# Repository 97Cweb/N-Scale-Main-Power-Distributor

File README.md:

Main Power Distributor 

I supply these as is. You still need to use sense using them. If you burn down your place or hurt yourself, that's on you

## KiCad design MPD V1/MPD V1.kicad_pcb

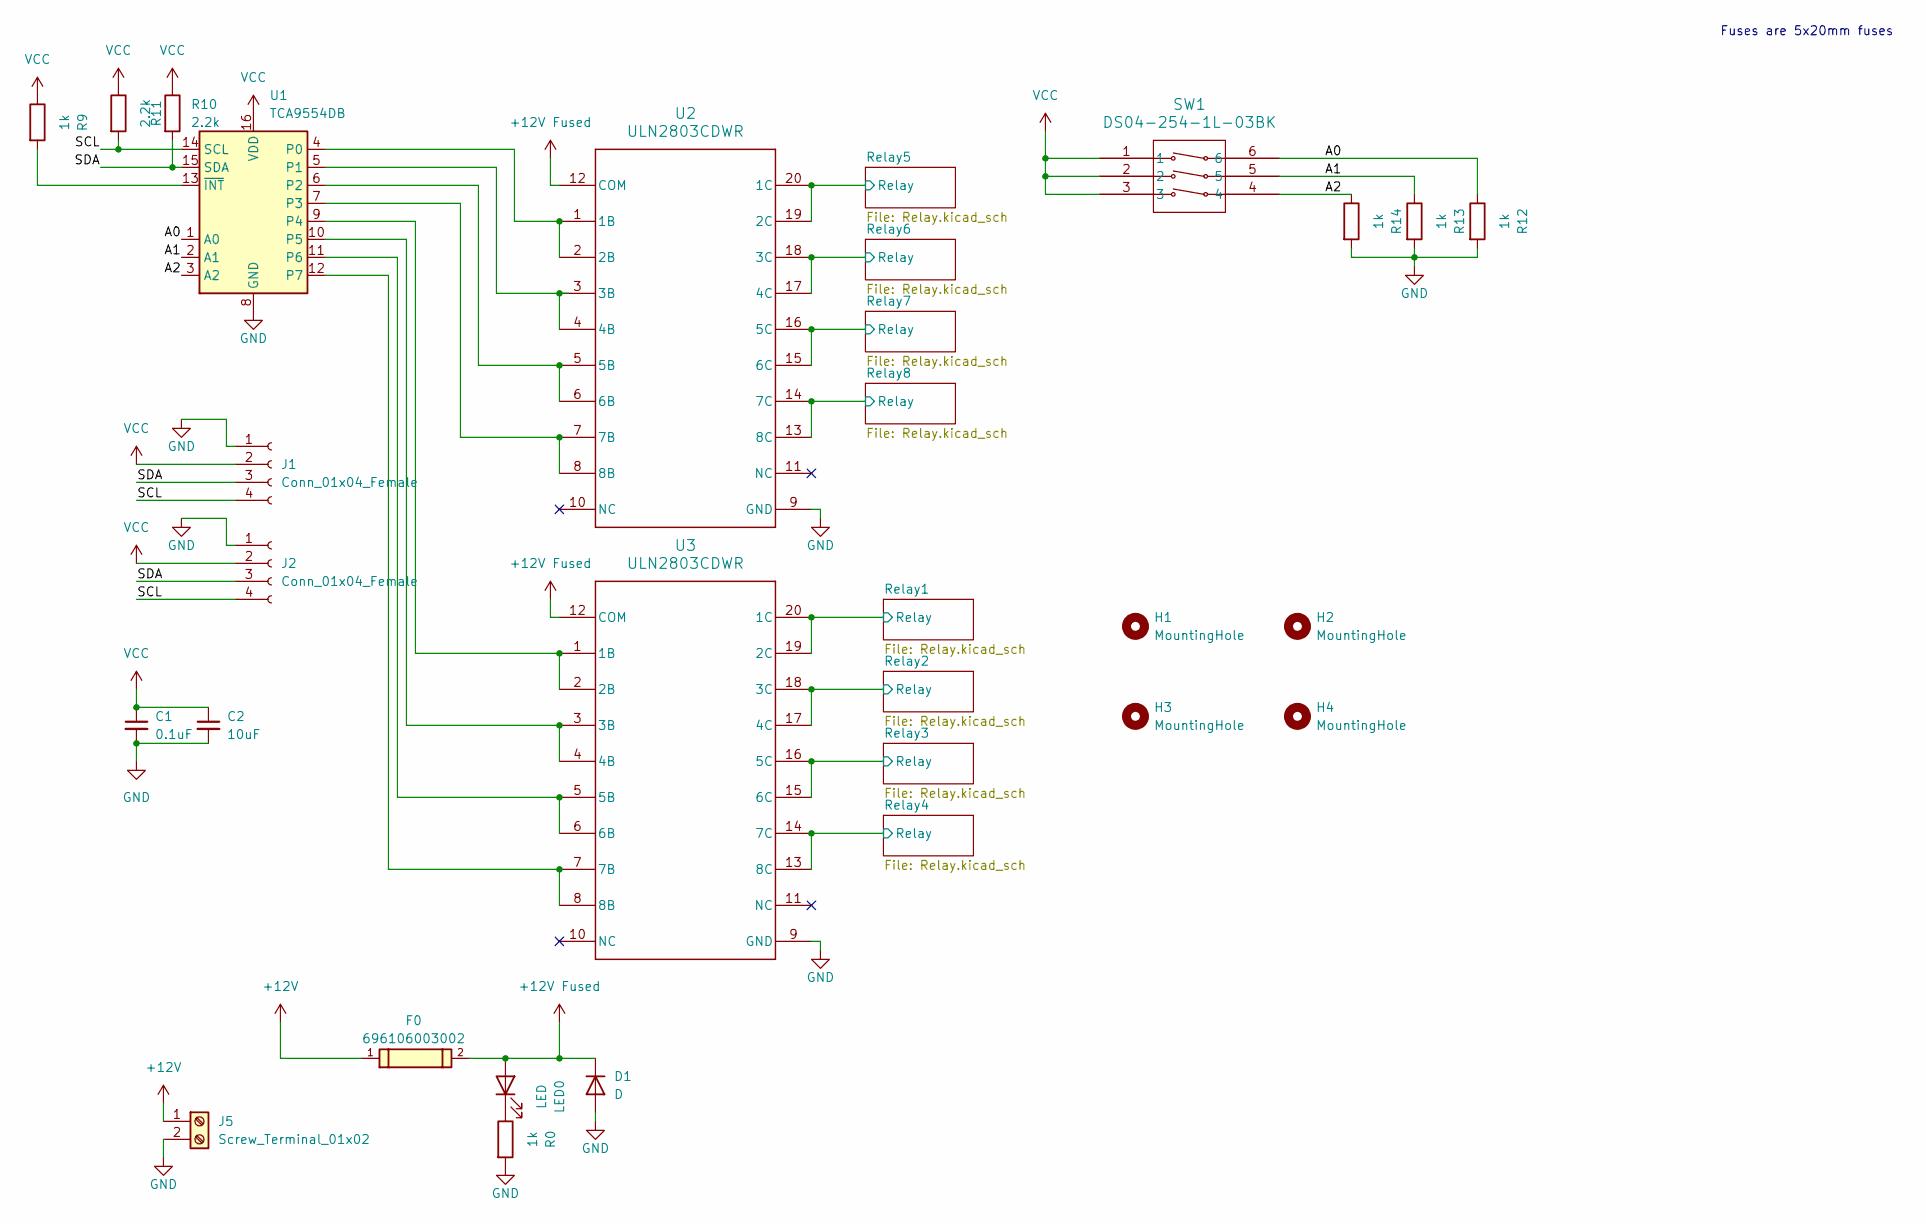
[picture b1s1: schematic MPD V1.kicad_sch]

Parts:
C1: 0.1uF; C_0603_1608Metric_Pad1.08x0.95mm_HandSolder
C2: 10uF; C_0603_1608Metric_Pad1.08x0.95mm_HandSolder
D1: D; D_A-405_P12.70mm_Horizontal
F0: 696106003002; PART-NUMBER 696106003002
H1, H2, H3, H4: MountingHole; MountingHole_3.2mm_M3
J1, J2: Conn_01x04_Female; JST_SH_SM04B-SRSS-TB_1x04-1MP_P1.00mm_Horizontal
J5: Screw_Terminal_01x02; TerminalBlock_bornier-2_P5.08mm
LED0: LED; LED_D5.0mm
R0, R9, R12, R13, R14: 1k; R_1206_3216Metric_Pad1.30x1.75mm_HandSolder
R10, R11: 2.2k; R_1206_3216Metric_Pad1.30x1.75mm_HandSolder
SW1: DS04-254-1L-03BK; DS04-254_CUD
U1: TCA9554DB; SSOP-16_5.3x6.2mm_P0.65mm
U2, U3: ULN2803CDWR; DW0020A-IPC_A

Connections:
+12V: F0.1, J5.1
+12V Fused: D1.1 (K), F0.2, LED0.2 (A), U2.12 (COM), U3.12 (COM); also elsewhere on the board
/A0: R12.1, SW1.6, U1.1 (A0)
/A1: R13.1, SW1.5, U1.2 (A1)
/A2: R14.1, SW1.4, U1.3 (A2)
/Relay1/Relay: U3.19 (2C), U3.20 (1C); also elsewhere on the board
/Relay2/Relay: U3.17 (4C), U3.18 (3C); also elsewhere on the board
/Relay3/Relay: U3.15 (6C), U3.16 (5C); also elsewhere on the board
/Relay4/Relay: U3.13 (8C), U3.14 (7C); also elsewhere on the board
/Relay5/Relay: U2.19 (2C), U2.20 (1C); also elsewhere on the board
/Relay6/Relay: U2.17 (4C), U2.18 (3C); also elsewhere on the board
/Relay7/Relay: U2.15 (6C), U2.16 (5C); also elsewhere on the board
/Relay8/Relay: U2.13 (8C), U2.14 (7C); also elsewhere on the board
/SCL: J1.4, J2.4, R11.2, U1.14 (SCL)
/SDA: J1.3, J2.3, R10.2, U1.15 (SDA)
GND: C1.2, C2.2, D1.2 (A), J1.1, J2.1, J5.2, R0.2, R12.2, R13.2, R14.2, U1.8 (GND), U2.9 (GND), U3.9 (GND); also elsewhere on the board
unnamed: LED0.1 (K), R0.1
unnamed: U1.4 (P0), U2.1 (1B), U2.2 (2B)
unnamed: U1.5 (P1), U2.3 (3B), U2.4 (4B)
unnamed: U1.6 (P2), U2.5 (5B), U2.6 (6B)
unnamed: U1.7 (P3), U2.7 (7B), U2.8 (8B)
unnamed: U1.9 (P4), U3.1 (1B), U3.2 (2B)
unnamed: U1.10 (P5), U3.3 (3B), U3.4 (4B)
unnamed: U1.11 (P6), U3.5 (5B), U3.6 (6B)
unnamed: U1.12 (P7), U3.7 (7B), U3.8 (8B)
unnamed: R9.2, U1.13 (~INT)
VCC: C1.1, C2.1, J1.2, J2.2, R9.1, R10.1, R11.1, SW1.1, SW1.2, SW1.3, U1.16 (VDD)

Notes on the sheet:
Fuses are 5x20mm fuses

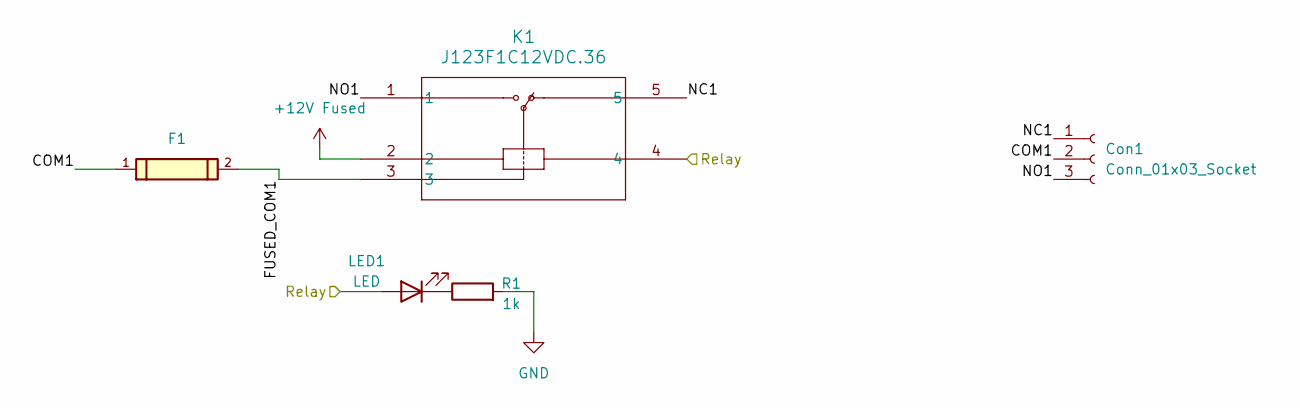
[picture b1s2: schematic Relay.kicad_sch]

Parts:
Con1: Conn_01x03_Socket; CONN_1757255_PXC
F1: 696106003002; PART-NUMBER 696106003002
K1: J123F1C12VDC.36; RELAY5_J123F1C5VDC.36_CRS with Cutout
LED1: LED; LED_D5.0mm
R1: 1k; R_1206_3216Metric_Pad1.30x1.75mm_HandSolder

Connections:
+12V Fused: K1.2; also elsewhere on the board
/Relay1/COM1: Con1.2, F1.1
/Relay1/FUSED_COM1: F1.2, K1.3
/Relay1/NC1: Con1.1, K1.5
/Relay1/NO1: Con1.3, K1.1
/Relay1/Relay: K1.4, LED1.2 (A); also elsewhere on the board
GND: R1.2; also elsewhere on the board
unnamed: LED1.1 (K), R1.1

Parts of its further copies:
Con2, Con3, Con4, Con5, Con6, Con7, Con8: Conn_01x03_Socket; CONN_1757255_PXC
F2, F3, F4, F5, F6, F7, F8: 696106003002; PART-NUMBER 696106003002
K2, K3, K4, K5, K6, K7, K8: J123F1C12VDC.36; RELAY5_J123F1C5VDC.36_CRS with Cutout
LED2, LED3, LED4, LED5, LED6, LED7, LED8: LED; LED_D5.0mm
R2, R3, R4, R5, R6, R7, R8: 1k; R_1206_3216Metric_Pad1.30x1.75mm_HandSolder

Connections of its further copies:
+12V Fused: K2.2, K3.2, K4.2, K5.2, K6.2, K7.2, K8.2; also elsewhere on the board
/Relay2/COM1: Con2.2, F2.1
/Relay2/FUSED_COM1: F2.2, K2.3
/Relay2/NC1: Con2.1, K2.5
/Relay2/NO1: Con2.3, K2.1
/Relay2/Relay: K2.4, LED2.2 (A); also elsewhere on the board
/Relay3/COM1: Con3.2, F3.1
/Relay3/FUSED_COM1: F3.2, K3.3
/Relay3/NC1: Con3.1, K3.5
/Relay3/NO1: Con3.3, K3.1
/Relay3/Relay: K3.4, LED3.2 (A); also elsewhere on the board
/Relay4/COM1: Con4.2, F4.1
/Relay4/FUSED_COM1: F4.2, K4.3
/Relay4/NC1: Con4.1, K4.5
/Relay4/NO1: Con4.3, K4.1
/Relay4/Relay: K4.4, LED4.2 (A); also elsewhere on the board
/Relay5/COM1: Con5.2, F5.1
/Relay5/FUSED_COM1: F5.2, K5.3
/Relay5/NC1: Con5.1, K5.5
/Relay5/NO1: Con5.3, K5.1
/Relay5/Relay: K5.4, LED5.2 (A); also elsewhere on the board
/Relay6/COM1: Con6.2, F6.1
/Relay6/FUSED_COM1: F6.2, K6.3
/Relay6/NC1: Con6.1, K6.5
/Relay6/NO1: Con6.3, K6.1
/Relay6/Relay: K6.4, LED6.2 (A); also elsewhere on the board
/Relay7/COM1: Con7.2, F7.1
/Relay7/FUSED_COM1: F7.2, K7.3
/Relay7/NC1: Con7.1, K7.5
/Relay7/NO1: Con7.3, K7.1
/Relay7/Relay: K7.4, LED7.2 (A); also elsewhere on the board
/Relay8/COM1: Con8.2, F8.1
/Relay8/FUSED_COM1: F8.2, K8.3
/Relay8/NC1: Con8.1, K8.5
/Relay8/NO1: Con8.3, K8.1
/Relay8/Relay: K8.4, LED8.2 (A); also elsewhere on the board
GND: R2.2, R3.2, R4.2, R5.2, R6.2, R7.2, R8.2; also elsewhere on the board
unnamed: LED2.1 (K), R2.1
unnamed: LED3.1 (K), R3.1
unnamed: LED4.1 (K), R4.1
unnamed: LED5.1 (K), R5.1
unnamed: LED6.1 (K), R6.1
unnamed: LED7.1 (K), R7.1
unnamed: LED8.1 (K), R8.1

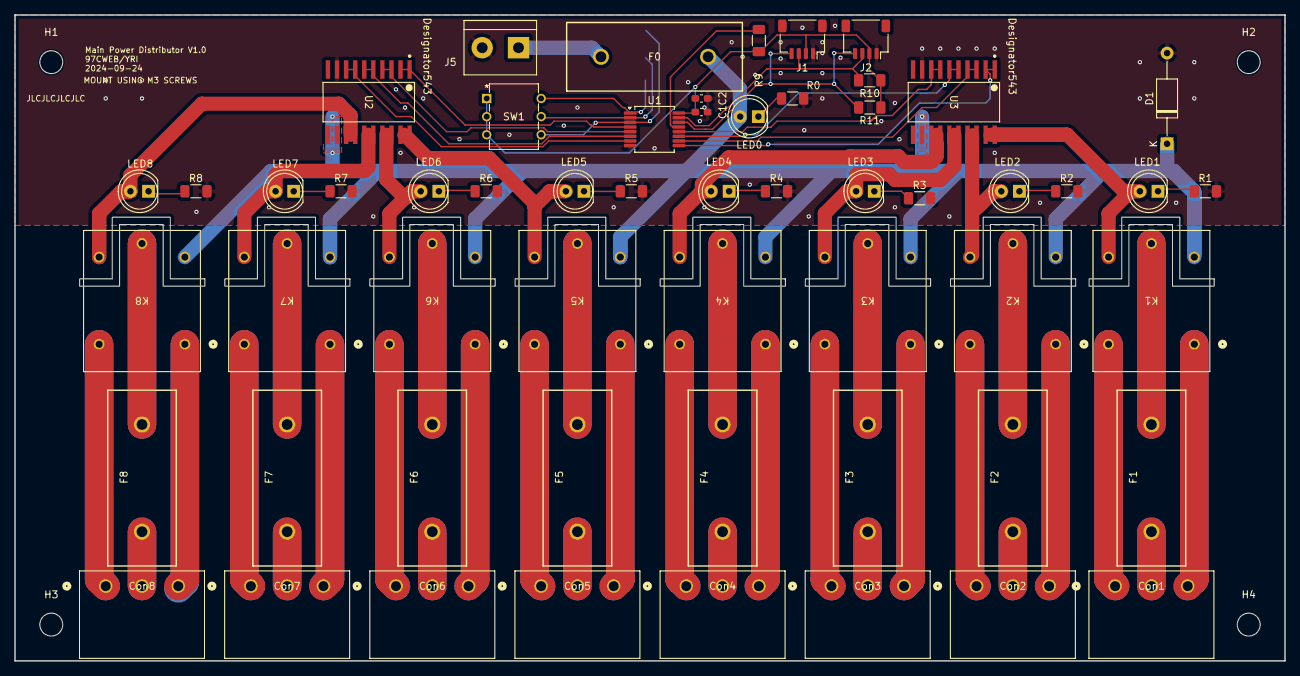
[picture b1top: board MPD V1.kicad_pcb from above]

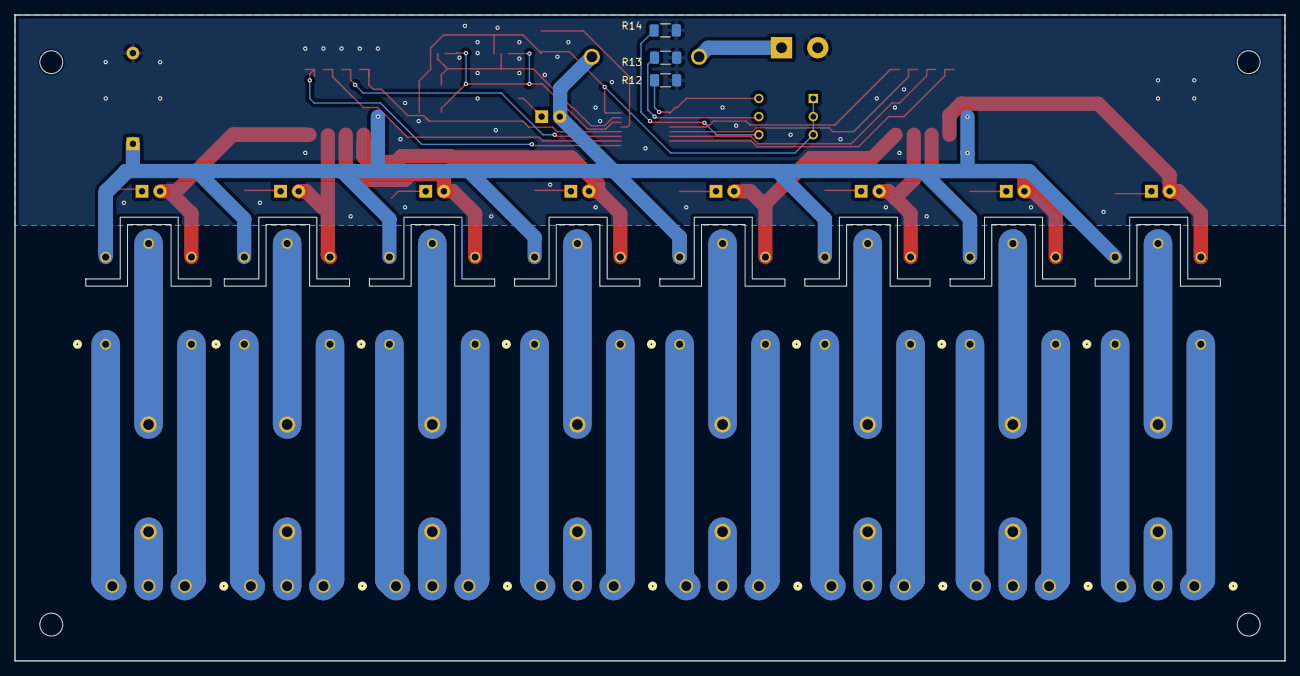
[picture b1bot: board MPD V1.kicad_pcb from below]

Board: 2 copper layers, 177.8 x 90.4 mm, 63 parts (3 on the bottom side), 67 nets.
